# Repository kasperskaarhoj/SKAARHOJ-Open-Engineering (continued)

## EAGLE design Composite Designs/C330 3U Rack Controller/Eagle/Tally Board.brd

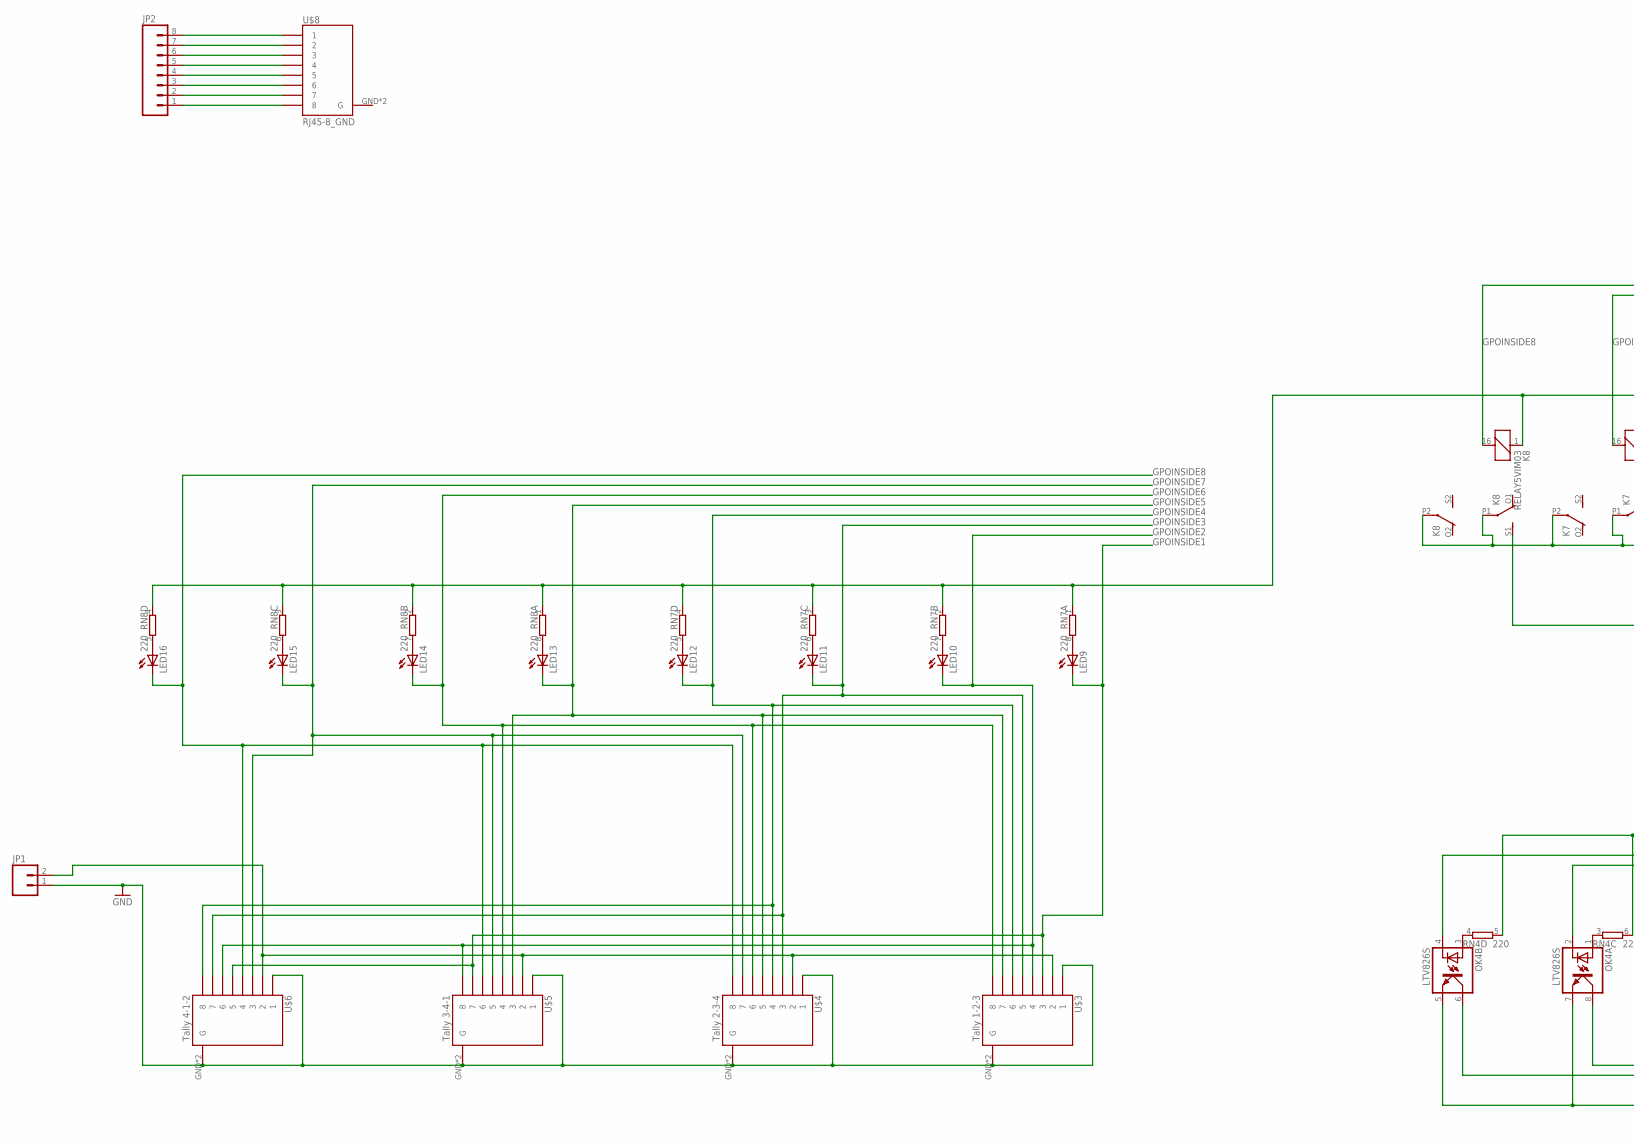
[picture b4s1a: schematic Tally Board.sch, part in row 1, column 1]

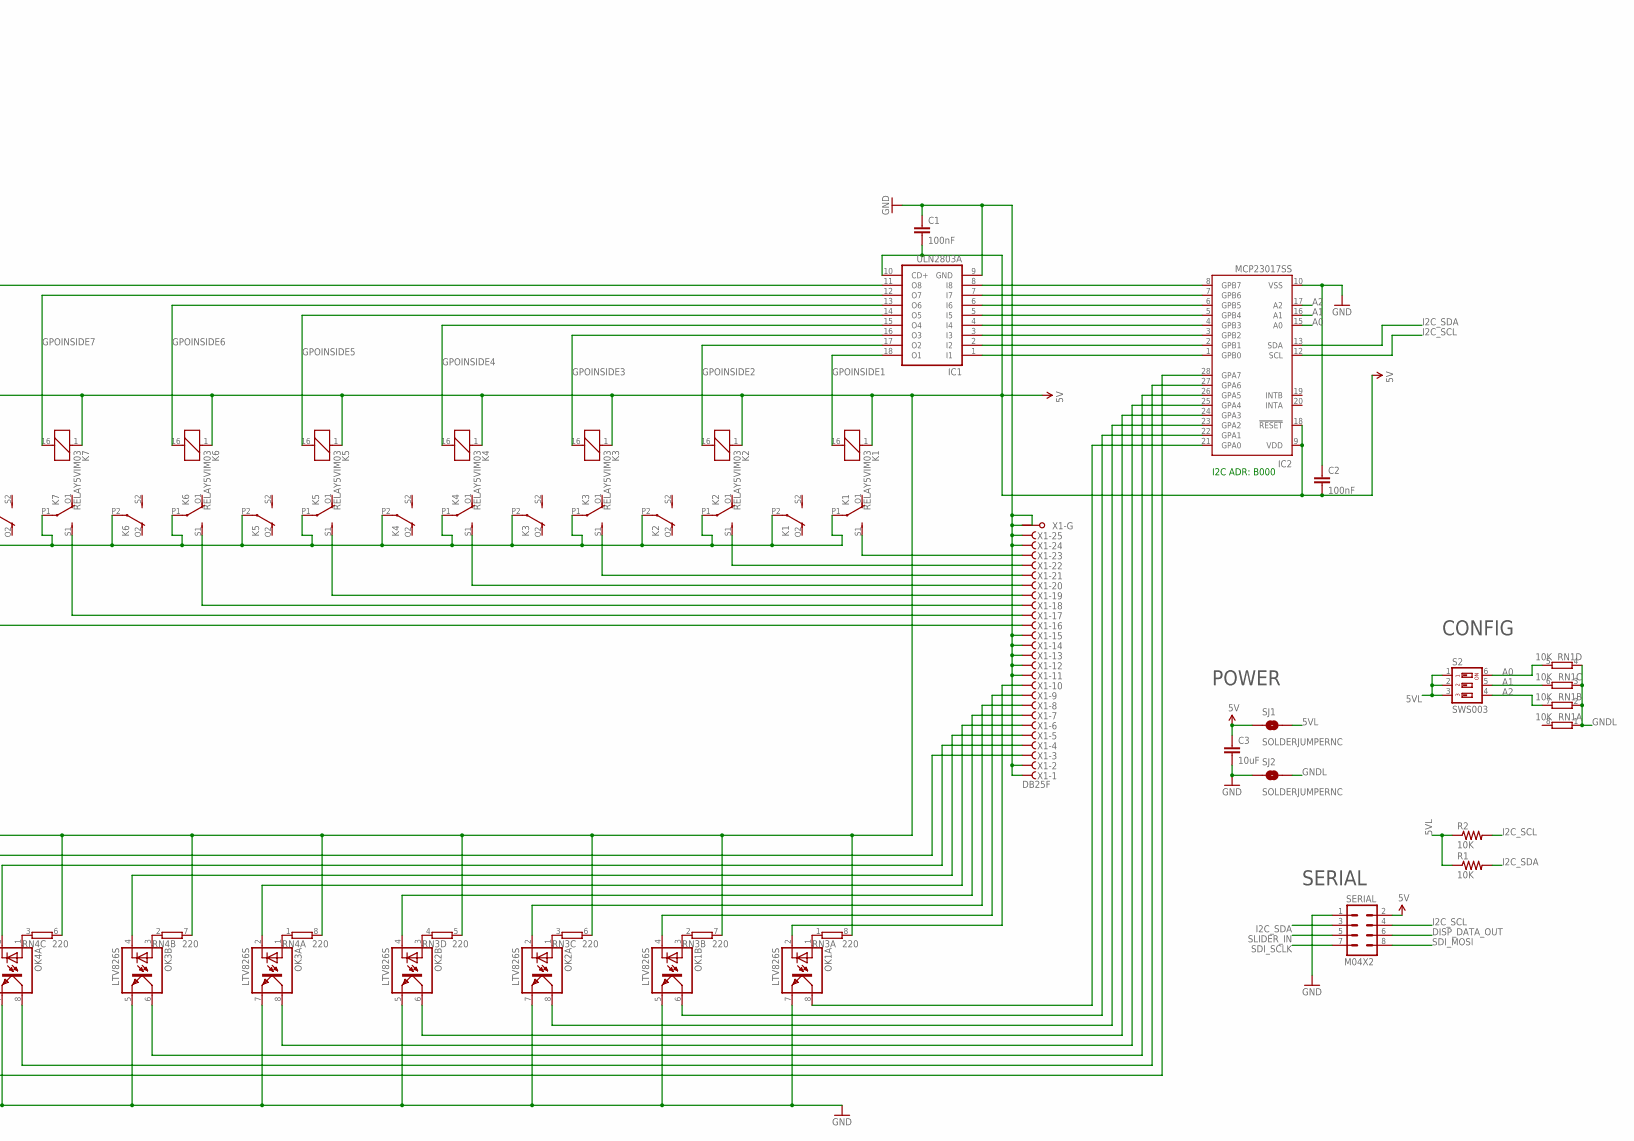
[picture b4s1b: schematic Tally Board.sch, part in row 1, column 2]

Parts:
C1: 100nF; 0805
C2: 100nF; 0603-CAP
C3: 10uF; 0805
IC1: ULN2803A; SO18W
IC2: MCP23017SS; SSOP28
JP1: M02PTH4; 1X02_XTRA_BIG
JP2: M081X08; 1X08
K1, K2, K3, K4, K5, K6, K7, K8: RELAY5VIM03; DS2Y
LED9, LED10, LED11, LED12, LED13, LED14, LED15, LED16: LED3MM
OK1, OK2, OK3, OK4: LTV826S; DIL8-SMD
R1, R2: 10K; 0603-RES
RN1: 10K; CAY16_HAND
RN3, RN4: 220; CAY16
RN7, RN8: 220; CAY16_HAND
S2: SWS003; SMS-003
SERIAL: M04X2; 2X4
SJ1, SJ2: SOLDERJUMPERNC; SJ_2S
U$3: Tally 1-2-3; RJ45-8_GND
U$4: Tally 2-3-4; RJ45-8_GND
U$5: Tally 3-4-1; RJ45-8_GND
U$6: Tally 4-1-2; RJ45-8_GND
U$8: RJ45-8_GND
X1: DB25F; F25HP

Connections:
5V: C1.2, C2.2, C3.1, IC1.10 (CD+), IC2.9 (VDD), IC2.18 (!RESET), K1.1, K2.1, K3.1, K4.1, K5.1, K6.1, K7.1, K8.1, RN3.5 (2), RN3.6 (2), RN3.7 (2), RN3.8 (2), RN4.5 (2), RN4.6 (2), RN4.7 (2), RN4.8 (2), RN7.1, RN7.2 (1), RN7.3 (1), RN7.4 (1), RN8.1, RN8.2 (1), RN8.3 (1), RN8.4 (1), SERIAL.2, SJ1.1
5VL: R1.1, R2.1, S2.1, S2.2, S2.3, SJ1.2
A0: IC2.15 (A0), RN1.5 (2), S2.6
A1: IC2.16 (A1), RN1.6 (2), S2.5
A2: IC2.17 (A2), RN1.7 (2), S2.4
DISP_DATA_OUT: SERIAL.6
G: U$8.GND (G), U$8.GND1 (G)
GNDL: RN1.1, RN1.2 (1), RN1.3 (1), RN1.4 (1), SJ2.2
GPOINSIDE1: IC1.18 (O1), K1.16 (2), LED9.K (C), U$3.3, U$5.7, U$6.5
GPOINSIDE2: IC1.17 (O2), K2.16 (2), LED10.K (C), U$3.4, U$5.8, U$6.6
GPOINSIDE3: IC1.16 (O3), K3.16 (2), LED11.K (C), U$3.5, U$4.3, U$6.7
GPOINSIDE4: IC1.15 (O4), K4.16 (2), LED12.K (C), U$3.6, U$4.4, U$6.8
GPOINSIDE5: IC1.14 (O5), K5.16 (2), LED13.K (C), U$3.7, U$4.5, U$5.3
GPOINSIDE6: IC1.13 (O6), K6.16 (2), LED14.K (C), U$3.8, U$4.6, U$5.4
GPOINSIDE7: IC1.12 (O7), K7.16 (2), LED15.K (C), U$4.7, U$5.5, U$6.3
GPOINSIDE8: IC1.11 (O8), K8.16 (2), LED16.K (C), U$4.8, U$5.6, U$6.4
I2C_SCL: IC2.12 (SCL), R2.2, SERIAL.4
I2C_SDA: IC2.13 (SDA), R1.2, SERIAL.3
unnamed: K1.S1 (S), X1.23 (F)
unnamed: JP2.8, U$8.1
unnamed: JP2.7, U$8.2
unnamed: JP2.6, U$8.3
unnamed: IC1.1 (I1), IC2.1 (GPB0)
unnamed: K2.S1 (S), X1.22 (F)
unnamed: JP2.5, U$8.4
unnamed: JP2.4, U$8.5
unnamed: JP2.3, U$8.6
unnamed: K3.S1 (S), X1.21 (F)
unnamed: JP2.2, U$8.7
unnamed: JP2.1, U$8.8
unnamed: K4.S1 (S), X1.20 (F)
unnamed: K5.S1 (S), X1.19 (F)
unnamed: K6.S1 (S), X1.18 (F)
unnamed: K7.S1 (S), X1.17 (F)
unnamed: LED9.A, RN7.8 (2)
unnamed: K8.S1 (S), X1.16 (F)
unnamed: LED10.A, RN7.7 (2)
unnamed: IC1.2 (I2), IC2.2 (GPB1)
unnamed: IC1.3 (I3), IC2.3 (GPB2)
unnamed: IC1.4 (I4), IC2.4 (GPB3)
unnamed: IC1.5 (I5), IC2.5 (GPB4)
unnamed: IC1.6 (I6), IC2.6 (GPB5)
unnamed: IC1.7 (I7), IC2.7 (GPB6)
unnamed: IC1.8 (I8), IC2.8 (GPB7)
unnamed: OK1.2 (C), X1.10 (F)
unnamed: OK1.1 (A), RN3.1
unnamed: IC2.21 (GPA0), OK1.8 (COL)
unnamed: OK1.3 (A), RN3.2 (1)
unnamed: OK2.1 (A), RN3.3 (1)
unnamed: OK2.3 (A), RN3.4 (1)
unnamed: OK3.2 (C), X1.6 (F)
unnamed: OK3.1 (A), RN4.1
unnamed: OK3.3 (A), RN4.2 (1)
unnamed: OK4.1 (A), RN4.3 (1)
unnamed: OK4.3 (A), RN4.4 (1)
unnamed: OK1.4 (C), X1.9 (F)
unnamed: OK2.2 (C), X1.8 (F)
unnamed: OK2.4 (C), X1.7 (F)
unnamed: IC2.28 (GPA7), OK4.6 (COL)
unnamed: OK3.4 (C), X1.5 (F)
unnamed: OK4.2 (C), X1.4 (F)
unnamed: OK4.4 (C), X1.3 (F)
unnamed: IC2.22 (GPA1), OK1.6 (COL)
unnamed: IC2.23 (GPA2), OK2.8 (COL)
unnamed: IC2.24 (GPA3), OK2.6 (COL)
unnamed: IC2.25 (GPA4), OK3.8 (COL)
unnamed: IC2.26 (GPA5), OK3.6 (COL)
unnamed: IC2.27 (GPA6), OK4.8 (COL)
unnamed: LED11.A, RN7.6 (2)
unnamed: LED12.A, RN7.5 (2)
unnamed: LED13.A, RN8.8 (2)
unnamed: LED14.A, RN8.7 (2)
unnamed: LED15.A, RN8.6 (2)
unnamed: LED16.A, RN8.5 (2)
unnamed: JP1.2, U$3.2, U$4.2, U$5.2, U$6.2
SDI_MOSI: SERIAL.8
SDI_SCLK: SERIAL.7
SLIDER_IN: SERIAL.5

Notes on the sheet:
I2C ADR: B000
SERIAL
POWER
CONFIG

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
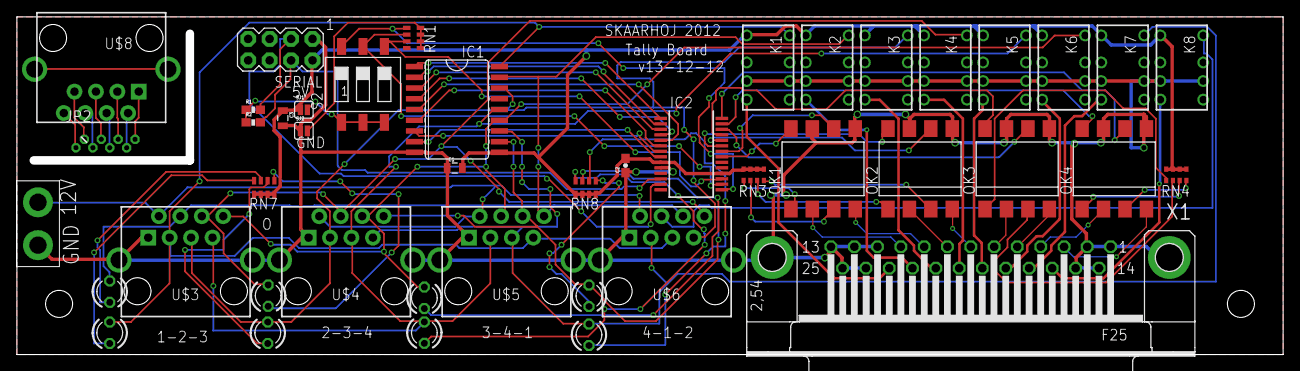
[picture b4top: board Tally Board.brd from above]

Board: 2 copper layers, 150.0 x 40.0 mm, 44 parts (0 on the bottom side), 75 nets.

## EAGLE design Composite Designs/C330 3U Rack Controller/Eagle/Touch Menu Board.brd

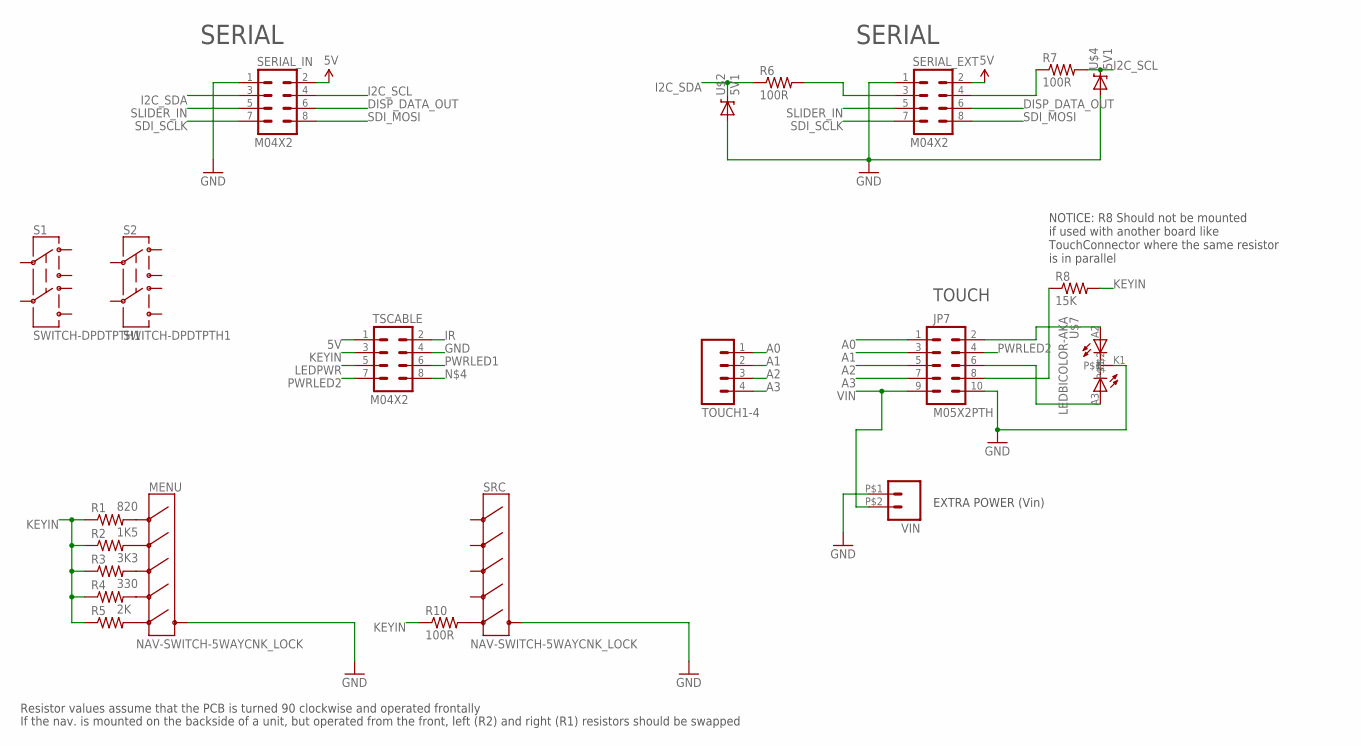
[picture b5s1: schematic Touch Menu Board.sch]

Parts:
JP7: M05X2PTH; AVR_ICSP
MENU: NAV-SWITCH-5WAYCNK_LOCK; NAV-SWITCH-5WAY
R1: 820; 0603-RES
R2: 1K5; 0603-RES
R3: 3K3; 0603-RES
R4: 330; 0603-RES
R5: 2K; 0603-RES
R6, R7, R10: 100R; 0603-RES
R8: 15K; 0603-RES
S1, S2: SWITCH-DPDTPTH1; TECONNECTIVITY-DPDT
SERIAL_EXT: M04X2; 2X4
SERIAL_IN: M04X2; 2X4
SRC: NAV-SWITCH-5WAYCNK_LOCK; NAV-SWITCH-5WAY
TOUCH1-4: M04PTH; 1X04
TSCABLE: M04X2; 2X4
U$2, U$4: 5V1; DIODE-ZENER
U$7: LEDBICOLOR-AKA; LED5MM-BICOLOR
VIN: M02PTH2; 1X02_BIG

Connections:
5V: SERIAL_EXT.2, SERIAL_IN.2, TSCABLE.1
A0: JP7.1, TOUCH1-4.1
A1: JP7.3, TOUCH1-4.2
A2: JP7.5, TOUCH1-4.3
A3: JP7.7, TOUCH1-4.4
DISP_DATA_OUT: SERIAL_EXT.6, SERIAL_IN.6
GND: JP7.10, MENU.PIN4 (COMMON), SERIAL_EXT.1, SERIAL_IN.1, SRC.PIN4 (COMMON), TSCABLE.4, U$2.P$2 (A), U$4.P$2 (A), U$7.K1, VIN.P$1 (1)
I2C_SCL: R7.2, SERIAL_IN.4, U$4.P$1 (C)
I2C_SDA: R6.1, SERIAL_IN.3, U$2.P$1 (C)
IR: TSCABLE.2
KEYIN: R1.1, R2.1, R3.1, R4.1, R5.1, R8.2, R10.1, TSCABLE.3
LEDPWR: TSCABLE.5
unnamed: R6.2, SERIAL_EXT.3
unnamed: MENU.PIN1 (UP), R1.2
unnamed: MENU.PIN3 (DWN), R2.2
unnamed: MENU.PIN2 (LEFT), R3.2
unnamed: MENU.PIN5 (RIGHT), R4.2
unnamed: JP7.2, U$7.A2
unnamed: JP7.6, U$7.A3
unnamed: MENU.PIN6 (PUSH), R5.2
unnamed: JP7.8, R8.1
unnamed: R10.2, SRC.PIN6 (PUSH)
unnamed: R7.1, SERIAL_EXT.4
PWRLED1: TSCABLE.6
PWRLED2: JP7.4, TSCABLE.7
SDI_MOSI: SERIAL_EXT.8, SERIAL_IN.8
SDI_SCLK: SERIAL_EXT.7, SERIAL_IN.7
SLIDER_IN: SERIAL_EXT.5, SERIAL_IN.5
VIN: JP7.9, VIN.P$2 (2)

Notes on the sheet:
TOUCH
EXTRA POWER (Vin)
SERIAL
Resistor values assume that the PCB is turned 90 clockwise and operated frontally
If the nav. is mounted on the backside of a unit, but operated from the front, left (R2) and right (R1) resistors should be swapped
NOTICE: R8 Should not be mounted if used with another board like TouchConnector where the same resistor is in parallel

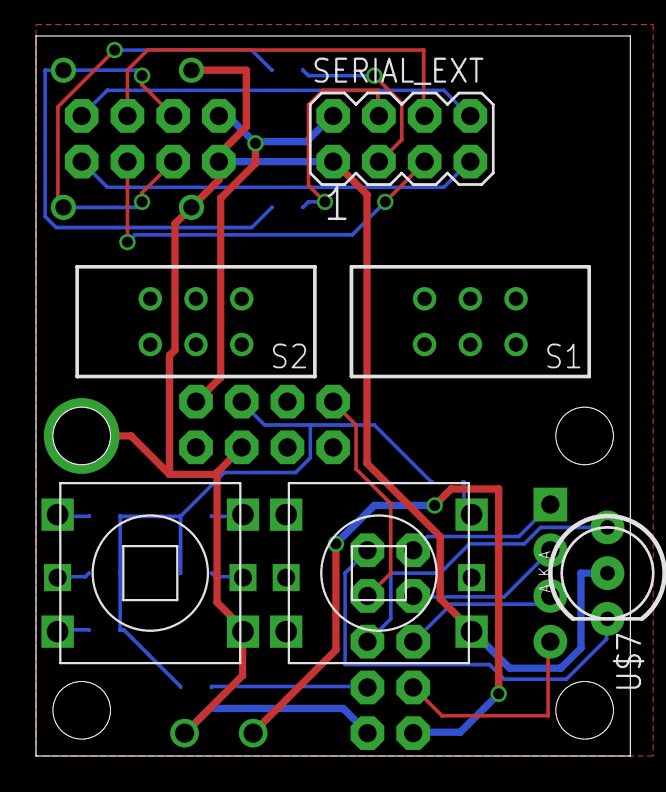
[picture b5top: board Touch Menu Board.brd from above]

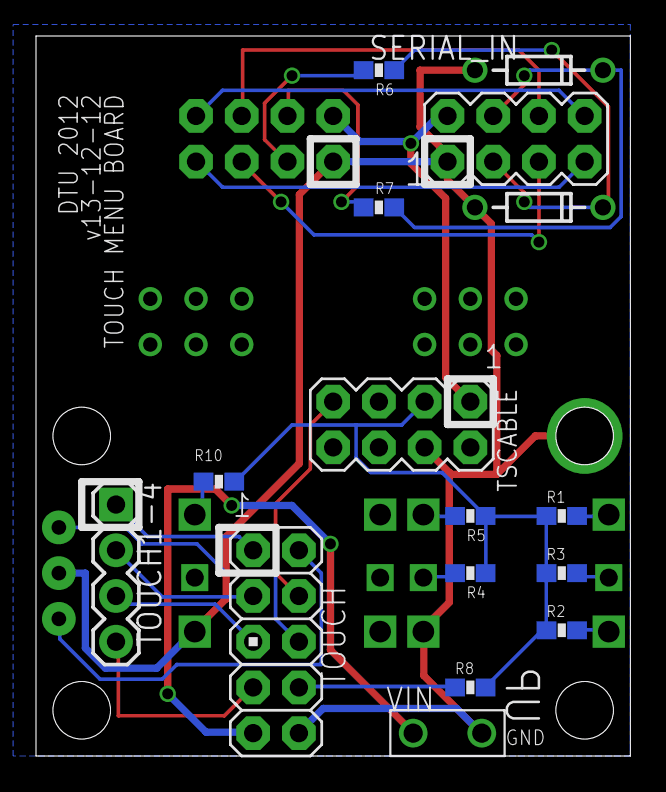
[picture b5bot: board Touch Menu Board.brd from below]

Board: 2 copper layers, 33.0 x 40.0 mm, 22 parts (16 on the bottom side), 26 nets.

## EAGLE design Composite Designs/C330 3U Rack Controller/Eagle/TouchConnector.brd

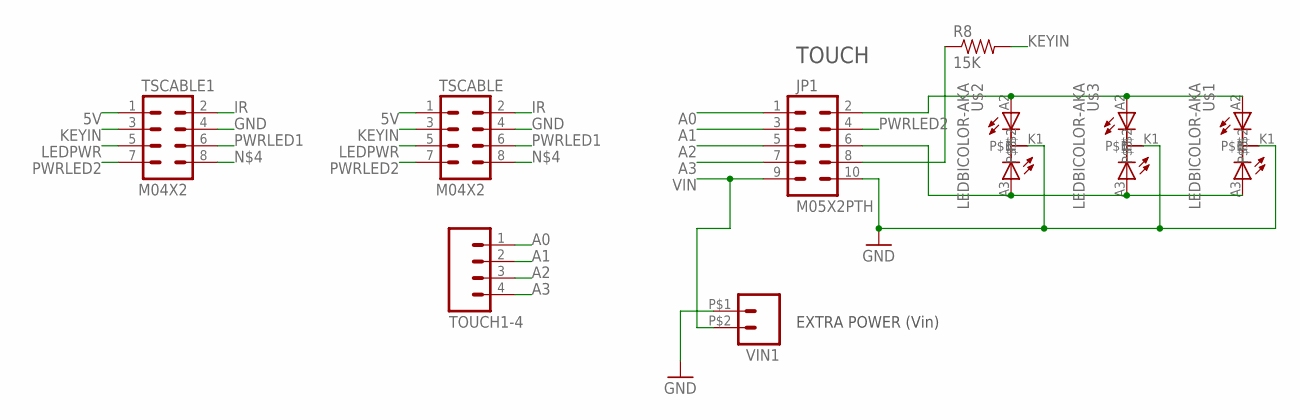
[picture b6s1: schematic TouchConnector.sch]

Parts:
JP1: M05X2PTH; AVR_ICSP
R8: 15K; 0603-RES
TOUCH1-4: M04PTH; 1X04
TSCABLE, TSCABLE1: M04X2; 2X4
U$1, U$2, U$3: LEDBICOLOR-AKA; LED5MM-BICOLOR
VIN1: M02PTH2; 1X02_BIG

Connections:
5V: TSCABLE.1, TSCABLE1.1
A0: JP1.1, TOUCH1-4.1
A1: JP1.3, TOUCH1-4.2
A2: JP1.5, TOUCH1-4.3
A3: JP1.7, TOUCH1-4.4
GND: JP1.10, TSCABLE.4, TSCABLE1.4, U$1.K1, U$2.K1, U$3.K1, VIN1.P$1 (1)
IR: TSCABLE.2, TSCABLE1.2
KEYIN: R8.2, TSCABLE.3, TSCABLE1.3
LEDPWR: TSCABLE.5, TSCABLE1.5
unnamed: JP1.2, U$1.A2, U$2.A2, U$3.A2
unnamed: JP1.6, U$1.A3, U$2.A3, U$3.A3
unnamed: TSCABLE.8, TSCABLE1.8
unnamed: JP1.8, R8.1
PWRLED1: TSCABLE.6, TSCABLE1.6
PWRLED2: JP1.4, TSCABLE.7, TSCABLE1.7
VIN: JP1.9, VIN1.P$2 (2)

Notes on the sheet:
TOUCH
EXTRA POWER (Vin)

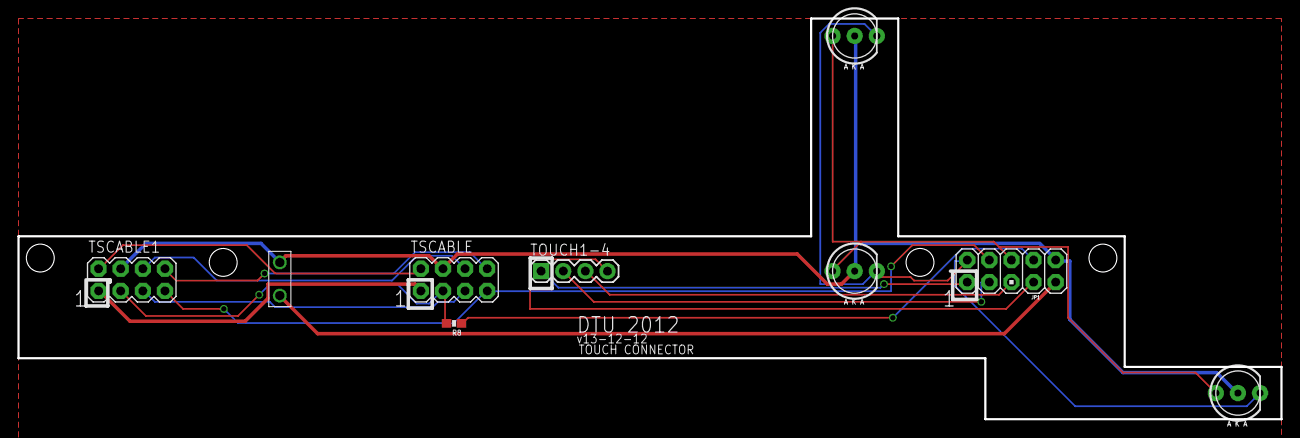
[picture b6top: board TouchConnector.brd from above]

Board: 2 copper layers, 145.0 x 46.0 mm, 9 parts (0 on the bottom side), 16 nets.
